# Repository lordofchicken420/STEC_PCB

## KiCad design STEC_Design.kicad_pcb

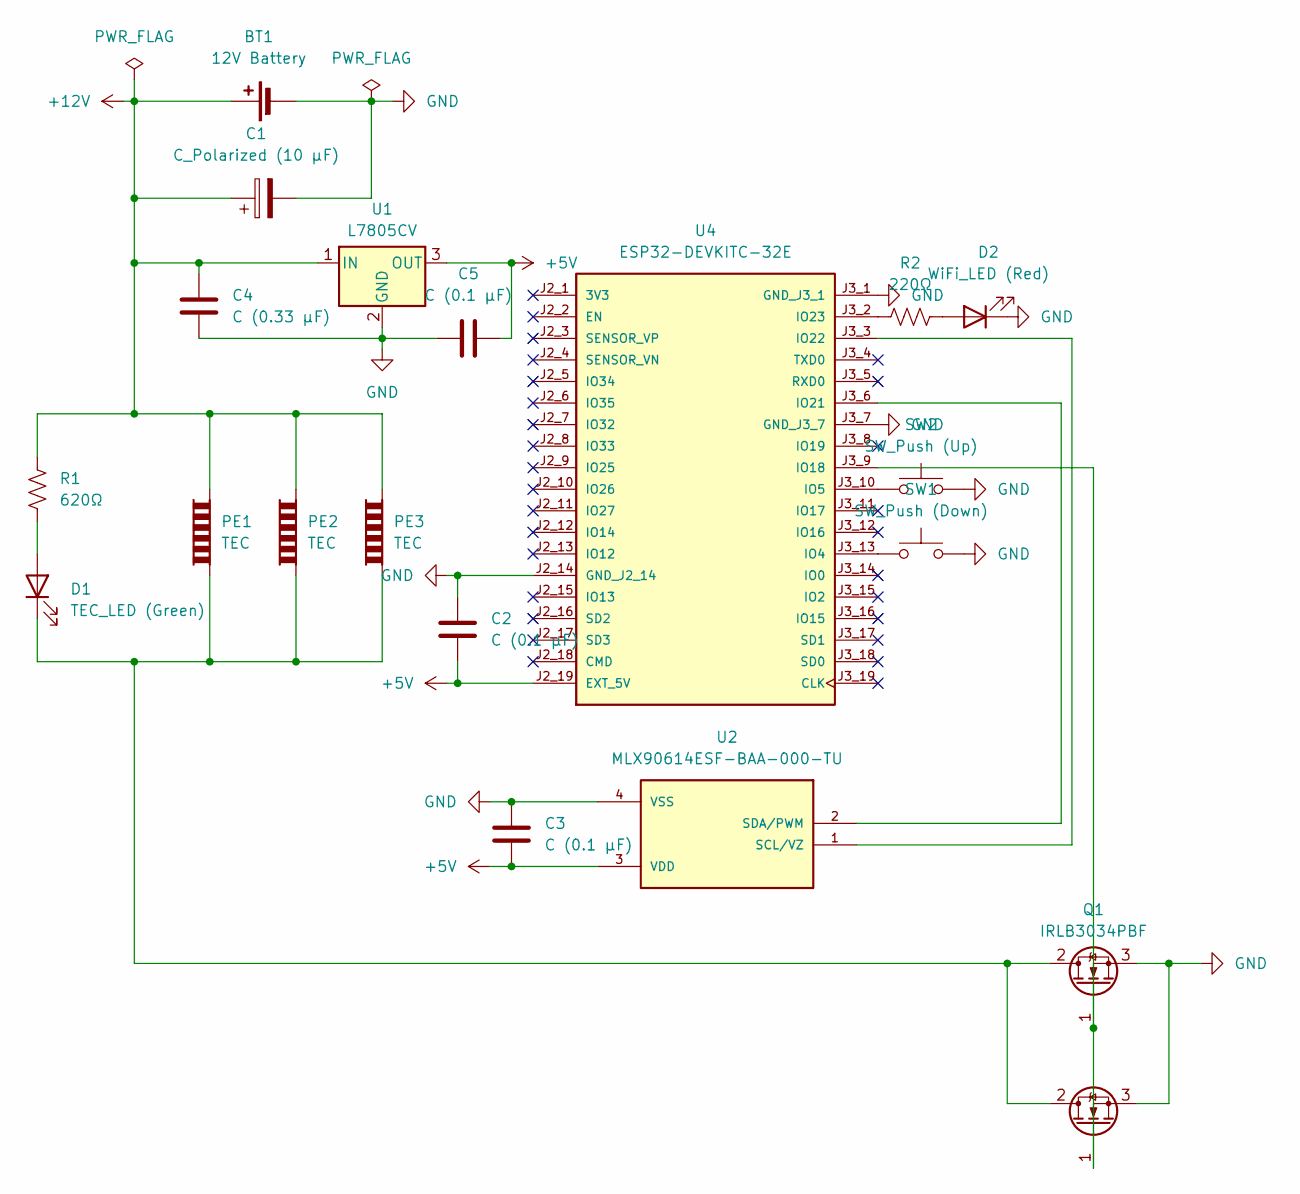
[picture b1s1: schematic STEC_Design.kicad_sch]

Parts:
BT1: 12V Battery; SolderWire-0.5sqmm_1x02_P4.8mm_D0.9mm_OD2.3mm
C1: C_Polarized (10 μF); CP_Radial_D5.0mm_P2.00mm
C2, C3, C5: C (0.1 μF); C_Disc_D4.3mm_W1.9mm_P5.00mm
C4: C (0.33 μF); C_Disc_D4.3mm_W1.9mm_P5.00mm
D1: TEC_LED (Green); LED_D5.0mm
D2: WiFi_LED (Red); LED_D5.0mm
PE1, PE2, PE3: TEC; SolderWire-0.75sqmm_1x02_P7mm_D1.25mm_OD3.5mm
Q1, Q2: IRLB3034PBF; TO254P1041X444X1930-3
R1: 620Ω; R_Axial_DIN0309_L9.0mm_D3.2mm_P12.70mm_Horizontal
R2: 220Ω; R_Axial_DIN0309_L9.0mm_D3.2mm_P12.70mm_Horizontal
SW1: SW_Push (Down); SW_PUSH_6mm_H4.3mm
SW2: SW_Push (Up); SW_PUSH_6mm_H4.3mm
U1: L7805CV; TO-220-3_Vertical
U2: MLX90614ESF-BAA-000-TU; TO254P942H425-4; PARTREV 13
U4: ESP32-DEVKITC-32E; MODULE_ESP32-DEVKITC-32E; PARTREV 1.4

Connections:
+5V: C2.2, C3.2, C5.2, U1.3 (OUT), U2.3 (VDD), U4.J2_19 (EXT_5V)
+12V: BT1.1 (+), C1.1, C4.1, PE1.2, PE2.2, PE3.2, R1.1, U1.1 (IN)
GND: BT1.2 (-), C1.2, C2.1, C3.1, C4.2, C5.1, D2.1 (K), Q1.3 (S), Q2.3 (S), SW1.2, SW2.2, U1.2 (GND), U2.4 (VSS), U4.J2_14 (GND_J2_14), U4.J3_1 (GND_J3_1), U4.J3_7 (GND_J3_7)
unnamed: D1.2 (A), R1.2
unnamed: D1.1 (K), PE1.1, PE2.1, PE3.1, Q1.2 (D), Q2.2 (D)
unnamed: D2.2 (A), R2.1
unnamed: Q1.1 (G), Q2.1 (G), U4.J3_9 (IO18)
unnamed: U2.1 (SCL/VZ), U4.J3_3 (IO22)
unnamed: U2.2 (SDA/PWM), U4.J3_6 (IO21)
unnamed: SW1.1, U4.J3_13 (IO4)
unnamed: SW2.1, U4.J3_10 (IO5)
unnamed: R2.2, U4.J3_2 (IO23)

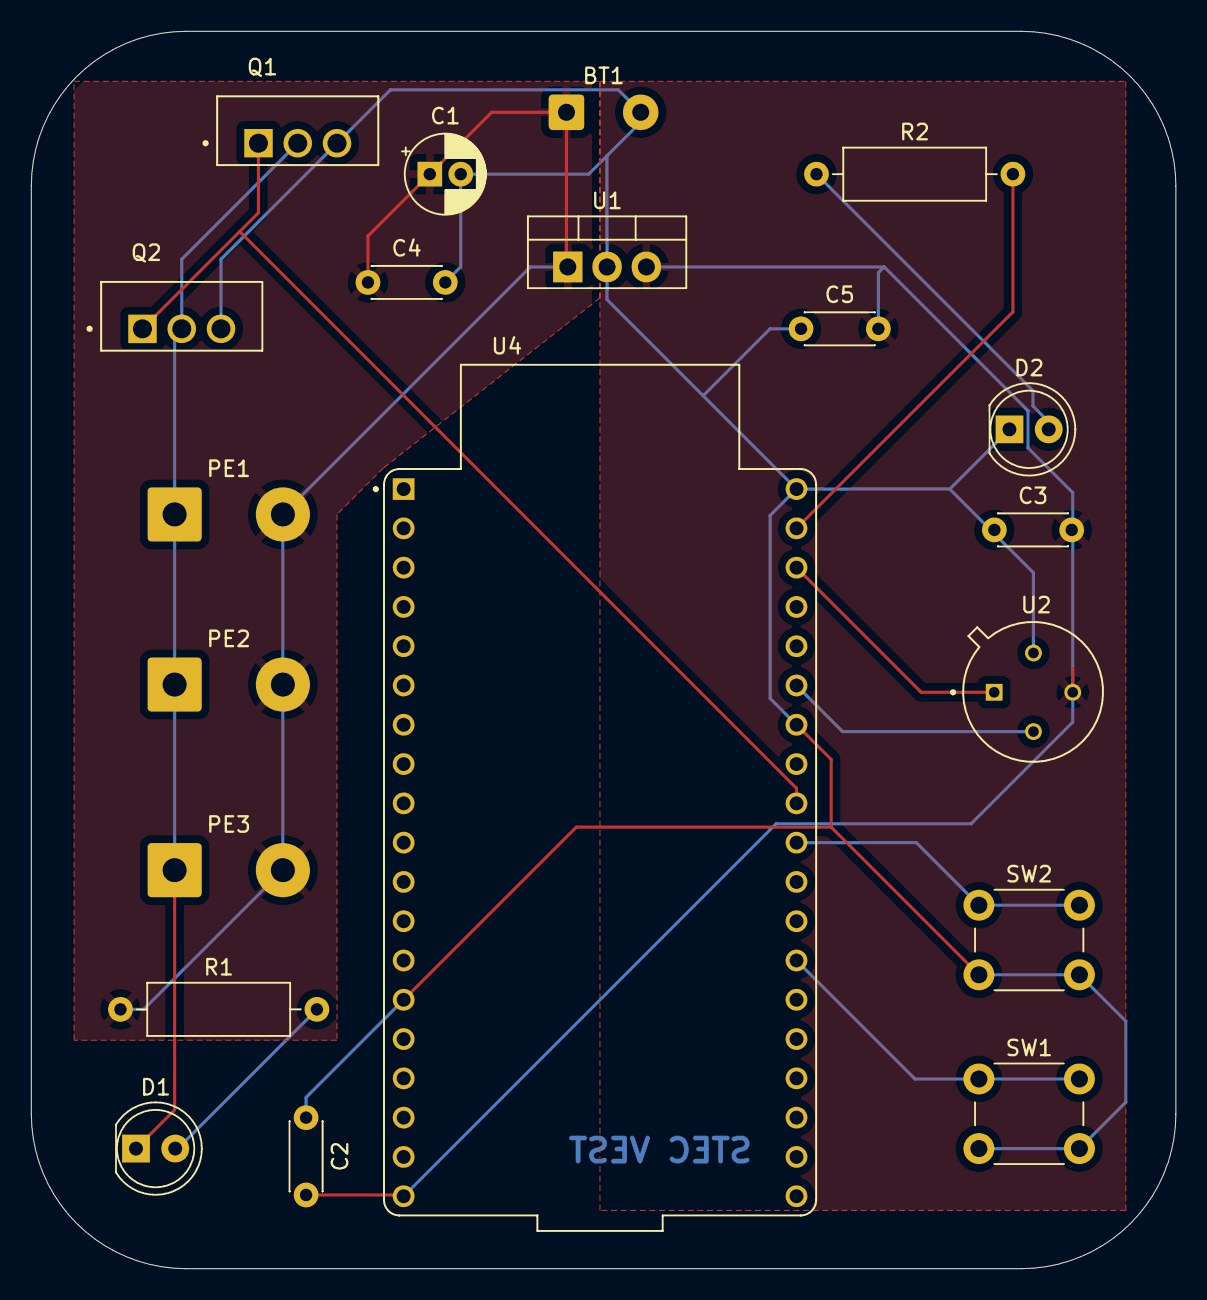
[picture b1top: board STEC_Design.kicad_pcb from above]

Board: 2 copper layers, 74.0 x 80.0 mm, 20 parts (0 on the bottom side), 12 nets.

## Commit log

2025-03-01 Initial commit of KiCad project
2025-03-01 added
2025-03-03 added_ESP32_DevBoard
2025-03-03 finalisedSchematics
2025-03-03 AddedPCBdesign
2025-03-03 finishedPCBdesign
2025-04-02 BeforePotentiometer
